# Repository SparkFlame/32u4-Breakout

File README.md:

# 32u4-Breakout

This hardware is released under a Creative Commons ShareAlike 4.0 License

The software is released under NO WARRANTY and under an MIT License

This board is made as a breakout for the [ATMega32u4](http://www.atmel.com/devices/atmega32u4.aspx).

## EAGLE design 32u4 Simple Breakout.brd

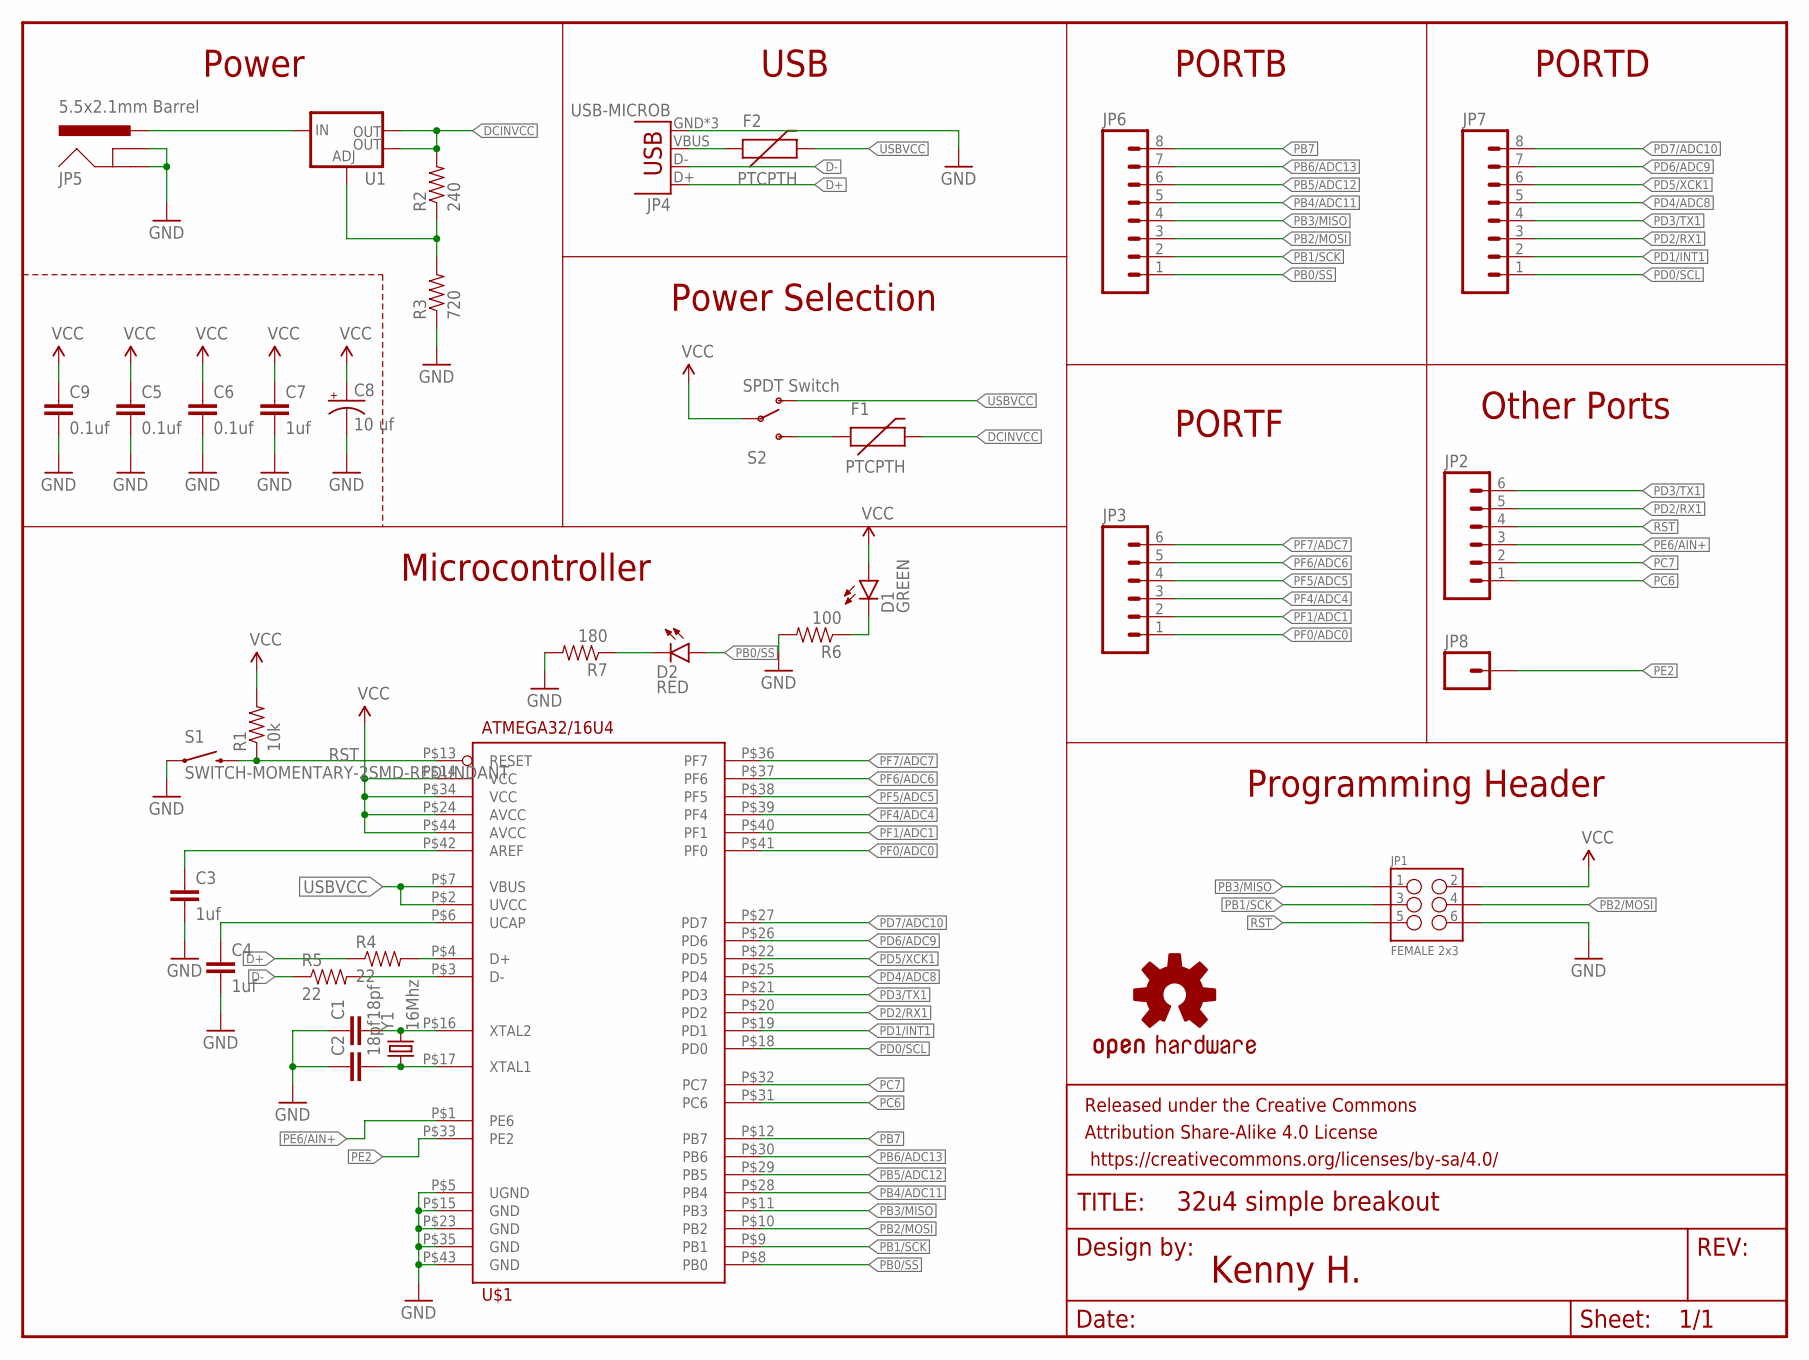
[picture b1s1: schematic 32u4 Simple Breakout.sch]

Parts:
C1, C2: 18pf; 0603-CAP
C3, C4, C7: 1uf; 0603-CAP
C5, C6, C9: 0.1uf; 0603-CAP
C8: 10 uf; CPOL-RADIAL-10UF-25V
D1: GREEN; LED-1206
D2: RED; LED-1206
F1, F2: PTCPTH; PTC
FRAME1: FRAME-LETTER; CREATIVE_COMMONS
JP1: FEMALE 2x3; 2X3
JP2, JP3: M06FEMALE_LOCK; 1X06_FEMALE_LOCK.010
JP4: USB-MICROB
JP5: 5.5x2.1mm Barrel; POWER_JACK_SMD
JP6, JP7: M08FEMALE_LOCK; 1X08_FEMALE_LOCK
JP8: M01PTH; 1X01
LOGO1: OSHW-LOGOM; OSHW-LOGO-M
R1: 10k; 0603-RES
R2: 240; 0603-RES
R3: 720; 0603-RES
R4, R5: 22; 0603-RES
R6: 100; 1206
R7: 180; 1206
S1: SWITCH-MOMENTARY-2SMD-REDUNDANT; TACTILE-SWITCH-SMD
S2: SPDT Switch; SWITCH-SPST-SMD-A
U1: V_REG_LM1117SOT223; SOT223
U$1: ATMEGA32/16U4; TQFP_44_0.8MM
Y1: 16Mhz; CRYSTAL-SMD-5X3

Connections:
D+: JP4.D+, R4.1
D-: JP4.D-, R5.1
DCINVCC: F1.P$2 (2), R2.2, U1.2 (OUT), U1.4 (OUT)
GND: C1.1, C2.1, C3.2, C4.2, C5.2, C6.2, C7.2, C8.2 (-), C9.2, JP1.6, JP4.GND, JP4.MT1 (GND), JP4.MT2 (GND), JP5.GND (GNDBREAK), JP5.P$4 (GND), R3.1, R6.2, R7.2, S1.1, S1.2 (1), U$1.P$5 (UGND), U$1.P$15 (GND), U$1.P$23 (GND), U$1.P$35 (GND), U$1.P$43 (GND)
unnamed: C3.1, U$1.P$42 (AREF)
unnamed: C4.1, U$1.P$6 (UCAP)
unnamed: R2.1, R3.2, U1.1 (ADJ)
unnamed: JP5.VIN0 (PWR), U1.3 (IN)
unnamed: R4.2, U$1.P$4 (D+)
unnamed: R5.2, U$1.P$3 (D-)
unnamed: F2.P$1 (1), JP4.VBUS
unnamed: F1.P$1 (1), S2.3 (S)
unnamed: D1.C, R6.1
unnamed: D2.C, R7.1
PB0/SS: D2.A, JP6.1, U$1.P$8 (PB0)
PB1/SCK: JP1.3, JP6.2, U$1.P$9 (PB1)
PB2/MOSI: JP1.4, JP6.3, U$1.P$10 (PB2)
PB3/MISO: JP1.1, JP6.4, U$1.P$11 (PB3)
PB4/ADC11: JP6.5, U$1.P$28 (PB4)
PB5/ADC12: JP6.6, U$1.P$29 (PB5)
PB6/ADC13: JP6.7, U$1.P$30 (PB6)
PB7: JP6.8, U$1.P$12 (PB7)
PC6: JP2.1, U$1.P$31 (PC6)
PC7: JP2.2, U$1.P$32 (PC7)
PD0/SCL: JP7.1, U$1.P$18 (PD0)
PD1/INT1: JP7.2, U$1.P$19 (PD1)
PD2/RX1: JP2.5, JP7.3, U$1.P$20 (PD2)
PD3/TX1: JP2.6, JP7.4, U$1.P$21 (PD3)
PD4/ADC8: JP7.5, U$1.P$25 (PD4)
PD5/XCK1: JP7.6, U$1.P$22 (PD5)
PD6/ADC9: JP7.7, U$1.P$26 (PD6)
PD7/ADC10: JP7.8, U$1.P$27 (PD7)
PE2: JP8.1, U$1.P$33 (PE2)
PE6/AIN+: JP2.3, U$1.P$1 (PE6)
PF0/ADC0: JP3.1, U$1.P$41 (PF0)
PF1/ADC1: JP3.2, U$1.P$40 (PF1)
PF4/ADC4: JP3.3, U$1.P$39 (PF4)
PF5/ADC5: JP3.4, U$1.P$38 (PF5)
PF6/ADC6: JP3.5, U$1.P$37 (PF6)
PF7/ADC7: JP3.6, U$1.P$36 (PF7)
RST: JP1.5, JP2.4, R1.1, S1.3 (2), S1.4 (2), U$1.P$13 (RESET)
USBVCC: F2.P$2 (2), S2.1 (O), U$1.P$2 (UVCC), U$1.P$7 (VBUS)
VCC: C5.1, C6.1, C7.1, C8.1 (+), C9.1, D1.A, JP1.2, R1.2, S2.2, U$1.P$14 (VCC), U$1.P$24 (AVCC), U$1.P$34 (VCC), U$1.P$44 (AVCC)
XTAL1: C2.2, U$1.P$17 (XTAL1), Y1.1
XTAL2: C1.2, U$1.P$16 (XTAL2), Y1.3 (2)

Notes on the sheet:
Microcontroller
PORTB
PORTD
PORTF
Other Ports
Power
USB
Programming Header
Power Selection
Kenny H.

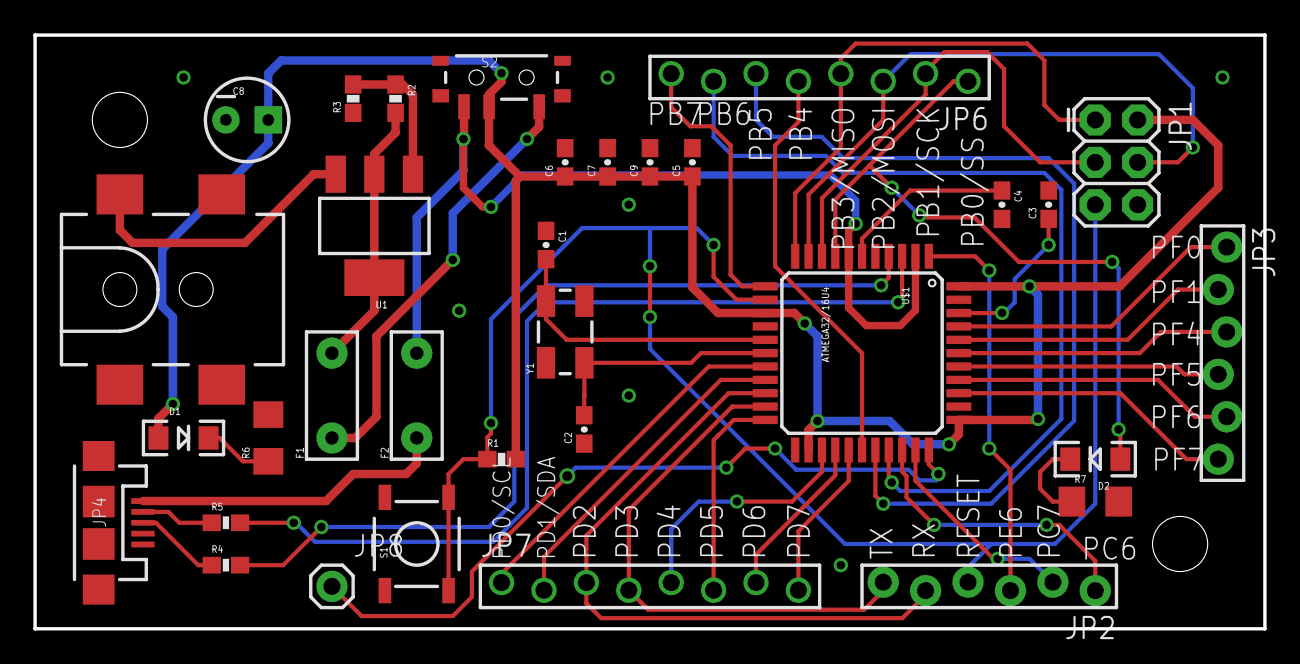
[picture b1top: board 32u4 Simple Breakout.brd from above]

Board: 2 copper layers, 73.7 x 35.6 mm, 37 parts (1 on the bottom side), 45 nets.

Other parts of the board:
U$3, U$4: STAND-OFF

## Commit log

2016-03-09 Added files via upload
2016-03-09 Rename 32u4.Simple.Breakout.brd to Hardware/32u4.Simple.Breakout.brd
2016-03-09 Rename 32u4.Simple.Breakout.sch to Hardware/32u4.Simple.Breakout.sch
2016-03-11 Rename 32u4 Simple Breakout.brd to Hardware/32u4 Simple Breakout.brd
2016-03-11 Update 32u4 Simple Breakout BOM
2016-03-11 Update and rename 32u4 Simple Breakout BOM to Hardware/32u4 Simple Breakout BOM
2016-03-12 Rename 32u4 Simple Breakout.sch to Hardware/32u4 Simple Breakout.sch

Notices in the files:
parts and their libraries:
SparkFun-Capacitors: Licensing: Creative Commons ShareAlike 4.0 International - https://creativecommons.org/licenses/by-sa/4.0
SparkFun-Aesthetics: Released under the Creative Commons Attribution Share-Alike 4.0 License
SparkFun-Aesthetics: https://creativecommons.org/licenses/by-sa/4.0
